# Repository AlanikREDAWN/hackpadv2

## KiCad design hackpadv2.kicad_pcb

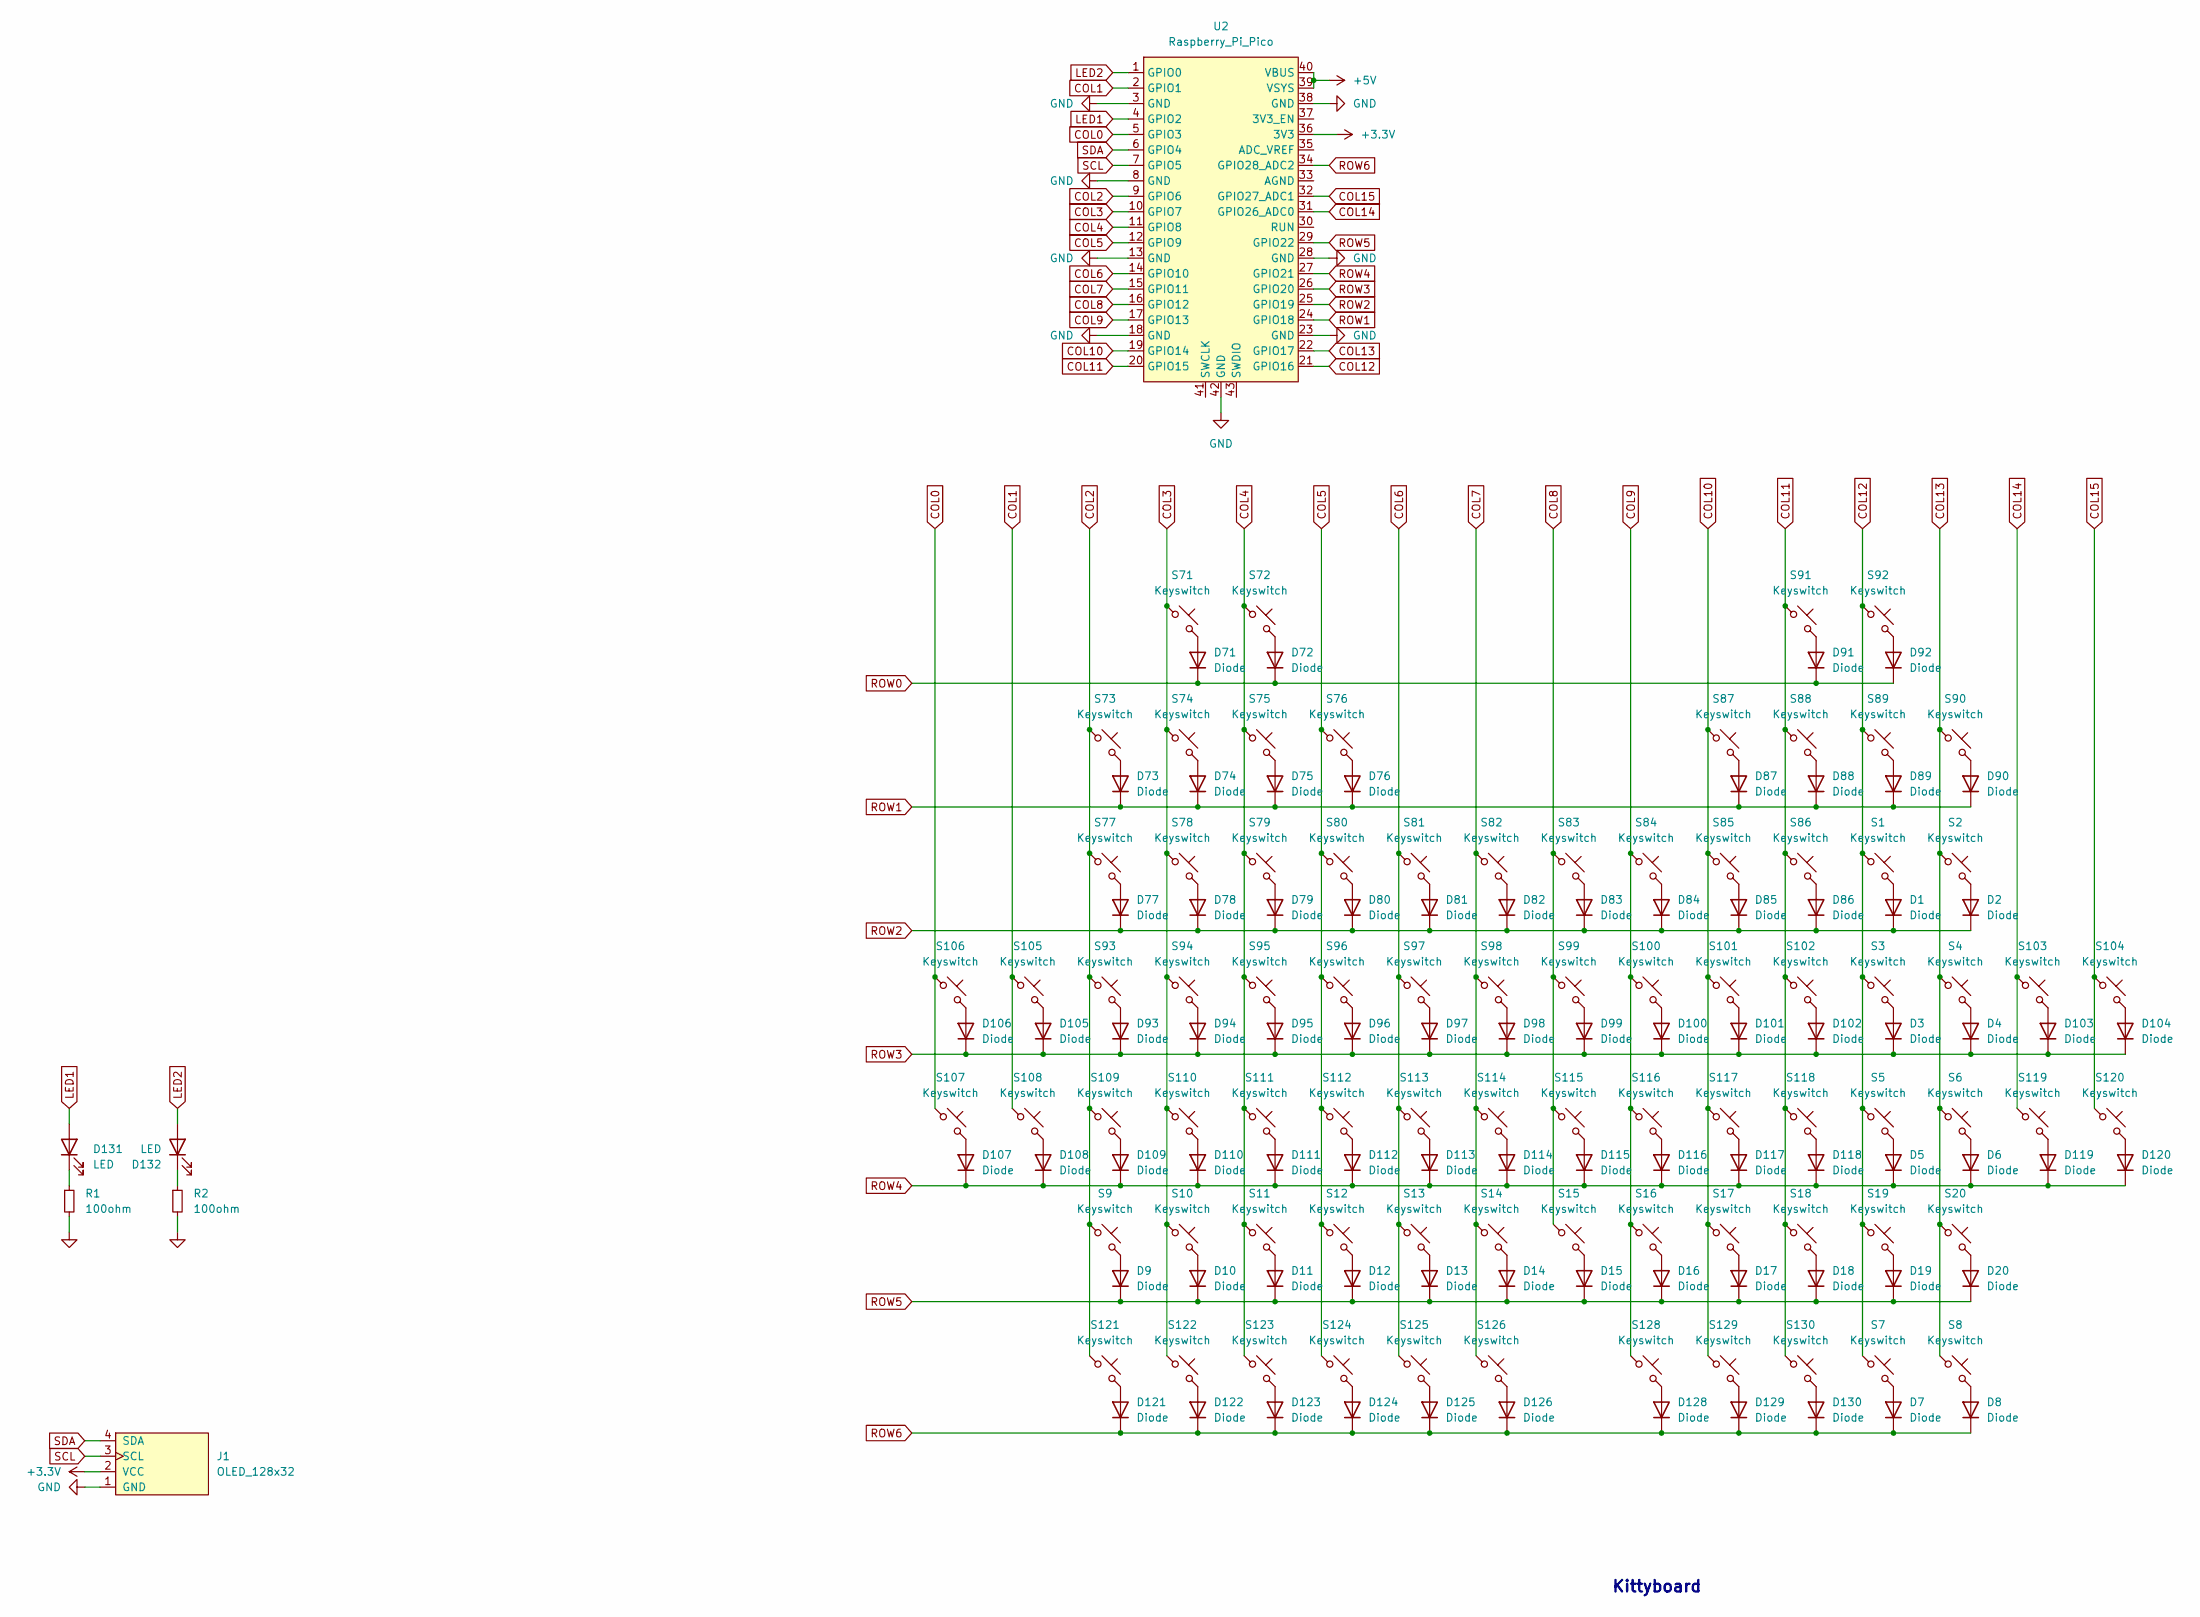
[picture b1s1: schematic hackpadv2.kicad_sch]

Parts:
D1, D2, D3, D4, D5, D6, D7, D8, D9, D10, D11, D12, D13, D14, D15, D16, D17, D18, D19, D20, D71, D72, D73, D74, D75, D76, D77, D78, D79, D80, D81, D82, D83, D84, D85, D86, D87, D88, D89, D90, D91, D92, D93, D94, D95, D96, D97, D98, D99, D100, D101, D102, D103, D104, D105, D106, D107, D108, D109, D110, D111, D112, D113, D114, D115, D116, D117, D118, D119, D120, D121, D122, D123, D124, D125, D126, D128, D129, D130: Diode; Diode_DO-35
D131, D132: LED; LED_D5.0mm
J1: OLED_128x32
R1, R2: 100ohm; YAG_PNP300_YAG
S1, S2, S3, S4, S5, S6, S7, S8, S9, S10, S11, S12, S13, S14, S15, S16, S17, S18, S19, S20, S71, S72, S73, S74, S75, S76, S77, S78, S79, S80, S81, S82, S83, S84, S85, S86, S87, S88, S89, S90, S91, S92, S93, S94, S95, S96, S97, S98, S99, S100, S101, S102, S103, S104, S105, S106, S107, S108, S109, S110, S111, S112, S113, S114, S115, S116, S117, S118, S119, S120, S121, S122, S123, S124, S125, S128, S129, S130: Keyswitch; MX_PCB_1.00u
S126: Keyswitch; MX_PCB_2.00u
U2: Raspberry_Pi_Pico

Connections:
+3.3V: J1.2 (VCC), U2.36 (3V3)
+5V: U2.39 (VSYS), U2.40 (VBUS)
COL0: S106.1, S107.1, U2.5 (GPIO3)
COL1: S105.1, S108.1, U2.2 (GPIO1)
COL2: S9.1, S73.1, S77.1, S93.1, S109.1, S121.1, U2.9 (GPIO6)
COL3: S10.1, S71.1, S74.1, S78.1, S94.1, S110.1, S122.1, U2.10 (GPIO7)
COL4: S11.1, S72.1, S75.1, S79.1, S95.1, S111.1, S123.1, U2.11 (GPIO8)
COL5: S12.1, S76.1, S80.1, S96.1, S112.1, S124.1, U2.12 (GPIO9)
COL6: S13.1, S81.1, S97.1, S113.1, S125.1, U2.14 (GPIO10)
COL7: S14.1, S82.1, S98.1, S114.1, S126.1, U2.15 (GPIO11)
COL8: S15.1, S83.1, S99.1, S115.1, U2.16 (GPIO12)
COL9: S16.1, S84.1, S100.1, S116.1, S128.1, U2.17 (GPIO13)
COL10: S17.1, S85.1, S87.1, S101.1, S117.1, S129.1, U2.19 (GPIO14)
COL11: S18.1, S86.1, S88.1, S91.1, S102.1, S118.1, S130.1, U2.20 (GPIO15)
COL12: S1.1, S3.1, S5.1, S7.1, S19.1, S89.1, S92.1, U2.21 (GPIO16)
COL13: S2.1, S4.1, S6.1, S8.1, S20.1, S90.1, U2.22 (GPIO17)
COL14: S103.1, S119.1, U2.31 (GPIO26_ADC0)
COL15: S104.1, S120.1, U2.32 (GPIO27_ADC1)
GND: J1.1 (GND), R1.2, R2.2, U2.3 (GND), U2.8 (GND), U2.13 (GND), U2.18 (GND), U2.23 (GND), U2.28 (GND), U2.38 (GND), U2.42 (GND)
LED1: D131.2 (A), U2.4 (GPIO2)
LED2: D132.2 (A), U2.1 (GPIO0)
unnamed: D1.2 (A), S1.2
unnamed: D2.2 (A), S2.2
unnamed: D3.2 (A), S3.2
unnamed: D4.2 (A), S4.2
unnamed: D5.2 (A), S5.2
unnamed: D6.2 (A), S6.2
unnamed: D7.2 (A), S7.2
unnamed: D8.2 (A), S8.2
unnamed: D9.2 (A), S9.2
unnamed: D10.2 (A), S10.2
unnamed: D11.2 (A), S11.2
unnamed: D12.2 (A), S12.2
unnamed: D13.2 (A), S13.2
unnamed: D14.2 (A), S14.2
unnamed: D15.2 (A), S15.2
unnamed: D16.2 (A), S16.2
unnamed: D17.2 (A), S17.2
unnamed: D18.2 (A), S18.2
unnamed: D19.2 (A), S19.2
unnamed: D20.2 (A), S20.2
unnamed: D71.2 (A), S71.2
unnamed: D72.2 (A), S72.2
unnamed: D73.2 (A), S73.2
unnamed: D74.2 (A), S74.2
unnamed: D75.2 (A), S75.2
unnamed: D76.2 (A), S76.2
unnamed: D77.2 (A), S77.2
unnamed: D78.2 (A), S78.2
unnamed: D79.2 (A), S79.2
unnamed: D80.2 (A), S80.2
unnamed: D81.2 (A), S81.2
unnamed: D82.2 (A), S82.2
unnamed: D83.2 (A), S83.2
unnamed: D84.2 (A), S84.2
unnamed: D85.2 (A), S85.2
unnamed: D86.2 (A), S86.2
unnamed: D87.2 (A), S87.2
unnamed: D88.2 (A), S88.2
unnamed: D89.2 (A), S89.2
unnamed: D90.2 (A), S90.2
unnamed: D91.2 (A), S91.2
unnamed: D92.2 (A), S92.2
unnamed: D93.2 (A), S93.2
unnamed: D94.2 (A), S94.2
unnamed: D95.2 (A), S95.2
unnamed: D96.2 (A), S96.2
unnamed: D97.2 (A), S97.2
unnamed: D98.2 (A), S98.2
unnamed: D99.2 (A), S99.2
unnamed: D100.2 (A), S100.2
unnamed: D101.2 (A), S101.2
unnamed: D102.2 (A), S102.2
unnamed: D103.2 (A), S103.2
unnamed: D104.2 (A), S104.2
unnamed: D105.2 (A), S105.2
unnamed: D106.2 (A), S106.2
unnamed: D107.2 (A), S107.2
unnamed: D108.2 (A), S108.2
unnamed: D109.2 (A), S109.2
unnamed: D110.2 (A), S110.2
unnamed: D111.2 (A), S111.2
unnamed: D112.2 (A), S112.2
unnamed: D113.2 (A), S113.2
unnamed: D114.2 (A), S114.2
unnamed: D115.2 (A), S115.2
unnamed: D116.2 (A), S116.2
unnamed: D117.2 (A), S117.2
unnamed: D118.2 (A), S118.2
unnamed: D119.2 (A), S119.2
unnamed: D120.2 (A), S120.2
unnamed: D121.2 (A), S121.2
unnamed: D122.2 (A), S122.2
unnamed: D123.2 (A), S123.2
unnamed: D124.2 (A), S124.2
unnamed: D125.2 (A), S125.2
unnamed: D126.2 (A), S126.2
unnamed: D128.2 (A), S128.2
unnamed: D129.2 (A), S129.2
unnamed: D130.2 (A), S130.2
unnamed: D131.1 (K), R1.1
unnamed: D132.1 (K), R2.1
ROW0: D71.1 (K), D72.1 (K), D91.1 (K), D92.1 (K)
ROW1: D73.1 (K), D74.1 (K), D75.1 (K), D76.1 (K), D87.1 (K), D88.1 (K), D89.1 (K), D90.1 (K), U2.24 (GPIO18)
ROW2: D1.1 (K), D2.1 (K), D77.1 (K), D78.1 (K), D79.1 (K), D80.1 (K), D81.1 (K), D82.1 (K), D83.1 (K), D84.1 (K), D85.1 (K), D86.1 (K), U2.25 (GPIO19)
ROW3: D3.1 (K), D4.1 (K), D93.1 (K), D94.1 (K), D95.1 (K), D96.1 (K), D97.1 (K), D98.1 (K), D99.1 (K), D100.1 (K), D101.1 (K), D102.1 (K), D103.1 (K), D104.1 (K), D105.1 (K), D106.1 (K), U2.26 (GPIO20)
ROW4: D5.1 (K), D6.1 (K), D107.1 (K), D108.1 (K), D109.1 (K), D110.1 (K), D111.1 (K), D112.1 (K), D113.1 (K), D114.1 (K), D115.1 (K), D116.1 (K), D117.1 (K), D118.1 (K), D119.1 (K), D120.1 (K), U2.27 (GPIO21)
ROW5: D9.1 (K), D10.1 (K), D11.1 (K), D12.1 (K), D13.1 (K), D14.1 (K), D15.1 (K), D16.1 (K), D17.1 (K), D18.1 (K), D19.1 (K), D20.1 (K), U2.29 (GPIO22)
ROW6: D7.1 (K), D8.1 (K), D121.1 (K), D122.1 (K), D123.1 (K), D124.1 (K), D125.1 (K), D126.1 (K), D128.1 (K), D129.1 (K), D130.1 (K), U2.34 (GPIO28_ADC2)
SCL: J1.3 (SCL), U2.7 (GPIO5)
SDA: J1.4 (SDA), U2.6 (GPIO4)

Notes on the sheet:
Kittyboard

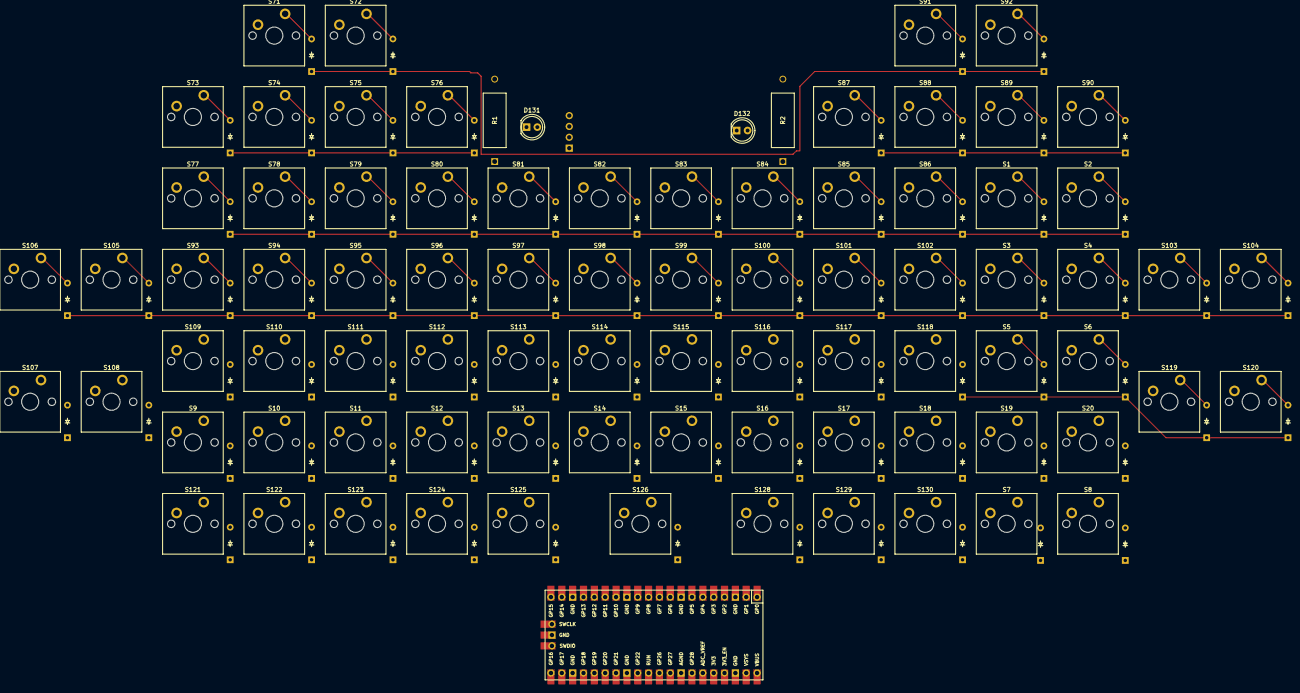
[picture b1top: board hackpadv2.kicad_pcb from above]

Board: 2 copper layers, 164 parts (0 on the bottom side), 111 nets.

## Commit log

2025-03-03 forgot to commit
